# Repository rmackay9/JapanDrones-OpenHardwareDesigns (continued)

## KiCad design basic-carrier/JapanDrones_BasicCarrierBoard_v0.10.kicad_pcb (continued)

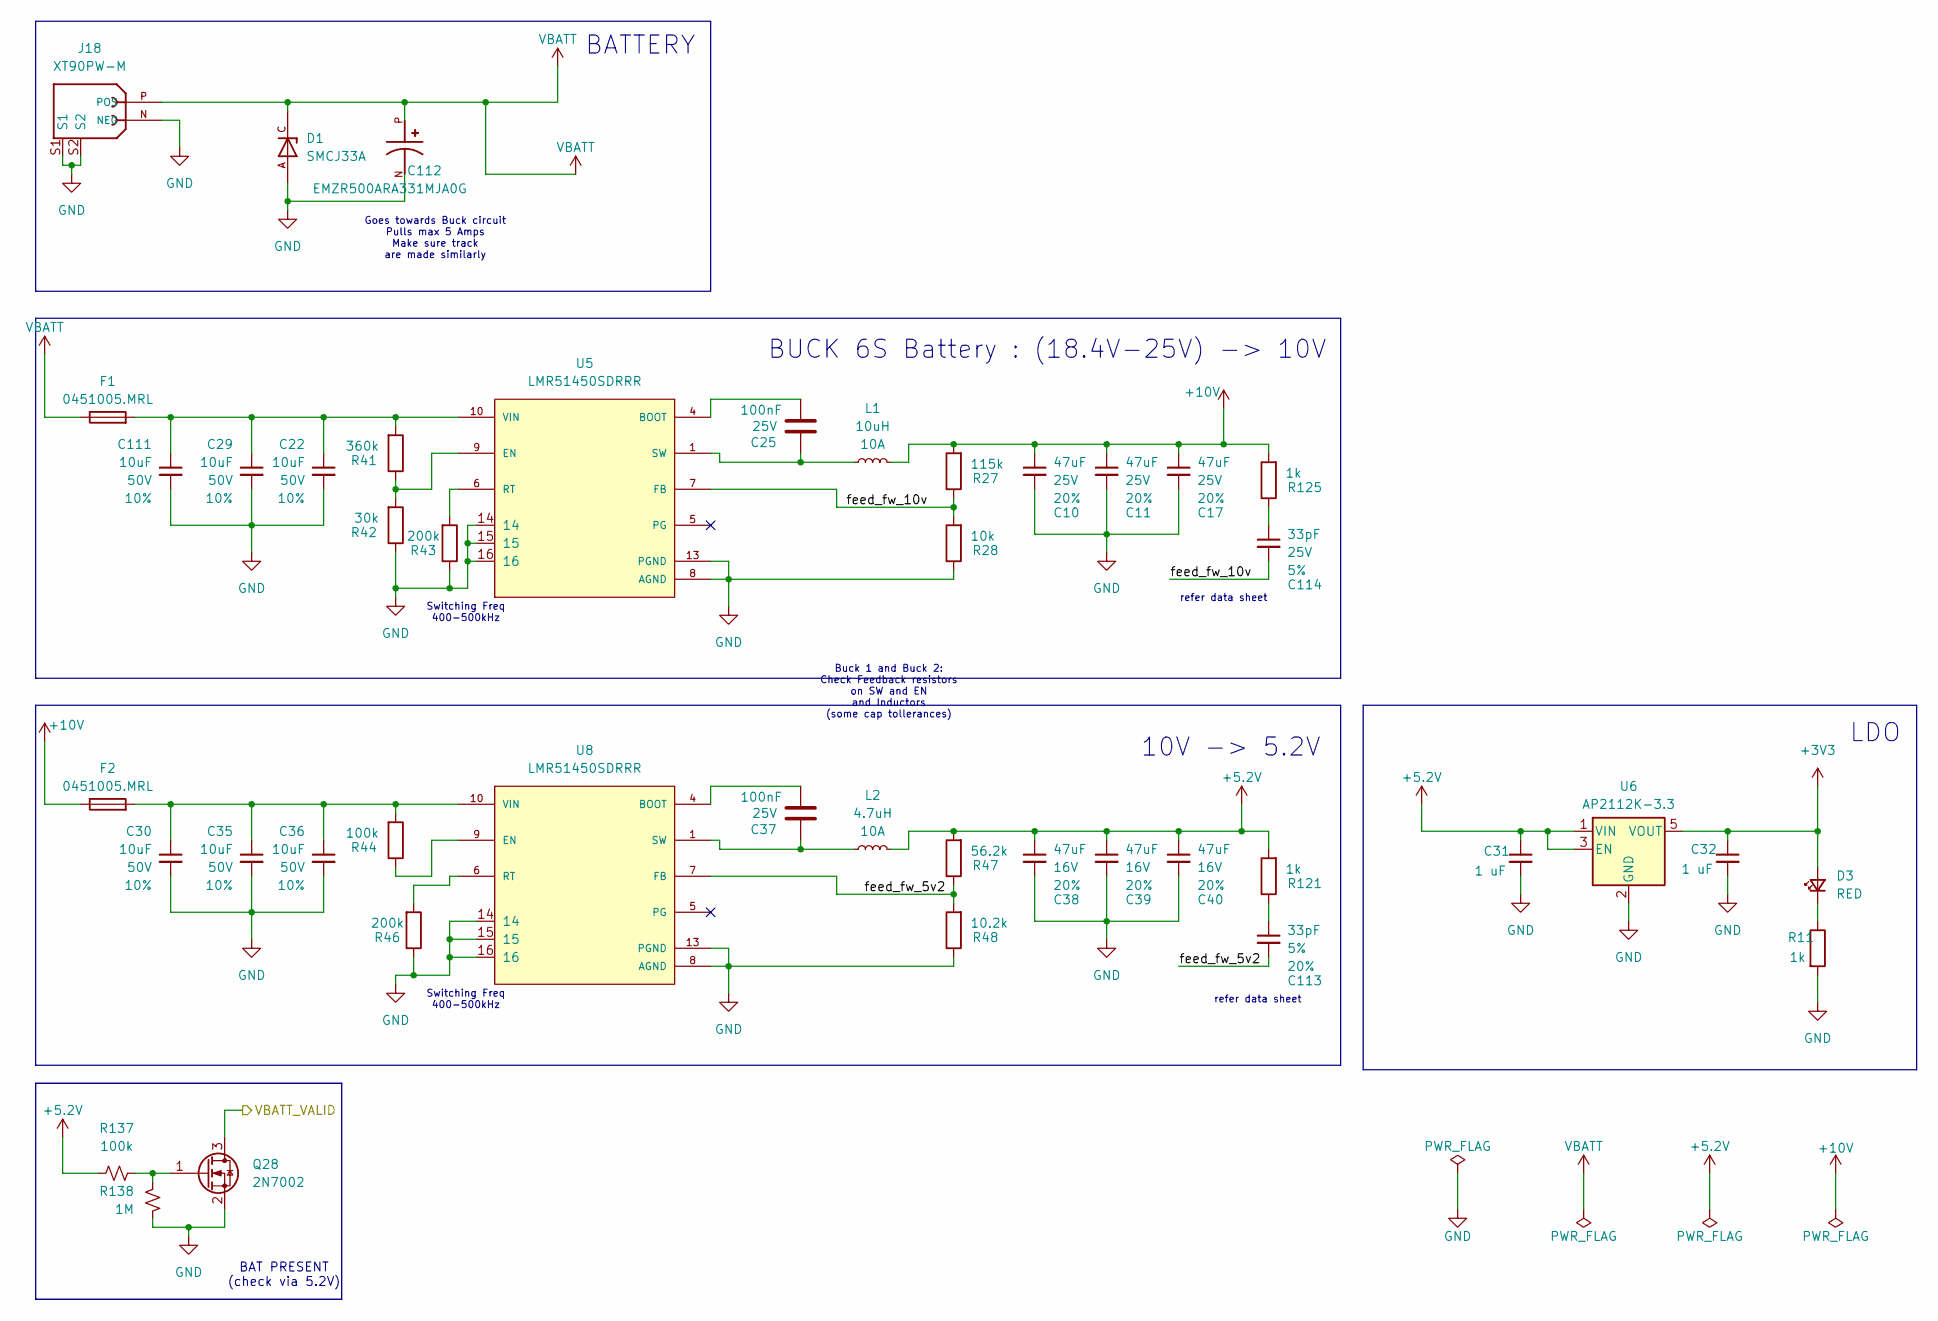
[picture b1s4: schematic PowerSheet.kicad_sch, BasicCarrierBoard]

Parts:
C10, C11, C17: 47uF; C_1206_3216Metric; Voltage 25V; Tolerance 20%; MPN GRM31CR61E476ME44L; LCSC C403725
C22, C29, C30, C35, C36, C111: 10uF; C_1206_3216Metric; Voltage 50V; Tolerance 10%; MPN CL31B106KBHNNNE; LCSC C89632
C25, C37: 100nF; C_0603_1608Metric; Voltage 25V; MPN CL10B104KB8NNNC; LCSC C1591
C31, C32: 1 uF; C_0603_1608Metric; Voltage 1kV; Tolerance 100%; MPN CL10B105KO8NNNC; LCSC Part C5673
C38, C39, C40: 47uF; C_1206_3216Metric; Voltage 16V; Tolerance 20%; MPN GRM31CR61E476ME44L; LCSC C403725
C112: EMZR500ARA331MJA0G; CAPAE1030X1050N; PARTREV N/A; LCSC C1845422
C113: 33pF; C_0603_1608Metric; Voltage 5%; Tolerance 20%; MPN CL10C330JB8NNNC; LCSC C1663
C114: 33pF; C_0603_1608Metric; Voltage 25V; Tolerance 5%; MPN CL10C330JB8NNNC; LCSC C1663
D1: SMCJ33A; DIOM6859X262N; PARTREV R2102; LCSC C42371548
D3: RED; LED_0603_1608Metric; MPN KT-0603R; LCSC Part C2286
F1, F2: 0451005.MRL; FUSC6125X236N; MPN 0451005.MRL; LCSC C48467
J18: XT90PW-M; AMASS_XT90PW-F; PARTREV V00; LCSC C3040689
L1: 10uH; COILMX MSY1040-100M-V; MPN MSY1040-100M-V; LCSC C49328996
L2: 4.7uH; APS1040M4R7H_4.7uh; MPN APS1040M4R7H; LCSC C49073686
Q28: 2N7002; SOT-23; MPN 2N7002; LCSC C8545
R11: 1k; R_0603_1608Metric; MPN 0603WAF1001T5E; LCSC Part C21190
R27: 115k; R_0603_1608Metric; MPN 0603WAF1153T5E; LCSC C22783
R28: 10k; R_0603_1608Metric; MPN 0603WAF1002T5E; LCSC C25804
R41: 360k; R_0603_1608Metric; MPN 0603WAF3603T5E; LCSC C23146
R42: 30k; R_0603_1608Metric; MPN 0603WAF3002T5E; LCSC C22984
R43, R46: 200k; R_0603_1608Metric; MPN 0603WAF2003T5E; LCSC C25811
R44: 100k; R_0603_1608Metric; MPN 0603WAF1003T5E; LCSC C25803
R47: 56.2k; R_0603_1608Metric; MPN 0603WAF5622T5E; LCSC C23080
R48: 10.2k; R_0603_1608Metric; MPN 0603WAF1022T5E; LCSC C22772
R121, R125: 1k; R_0603_1608Metric; MPN 0603WAF1001T5E; LCSC C21190
R137: 100k; R_0402_1005Metric; MPN 0402WGF1003TCE; LCSC C25741
R138: 1M; R_0402_1005Metric; MPN 0402WGF1004TCE; LCSC C26083
U5, U8: LMR51450SDRRR; CONV_LMR51450SDRRR; PARTREV December 2022; LCSC C6890985
U6: AP2112K-3.3; SOT-23-5_HandSoldering; MPN AP2112K-3.3TRG1; LCSC Part C23380830

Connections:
+3V3: C32.1, D3.2 (A), U6.5 (VOUT); also elsewhere on the board
+5.2V: C31.1, C38.1, C39.1, C40.1, L2.2, R47.2, R121.2, R137.1, U6.1 (VIN), U6.3 (EN); also elsewhere on the board
+10V: C10.1, C11.1, C17.1, F2.1, L1.2, R27.2, R125.2; also elsewhere on the board
/Connectors/VBATT_VALID: Q28.3 (D); also elsewhere on the board
/PowerSheet/feed_fw_5v2: C113.2, R47.1, R48.2, U8.7 (FB)
/PowerSheet/feed_fw_10v: C114.2, R27.1, R28.2, U5.7 (FB)
GND: C10.2, C11.2, C17.2, C22.2, C29.2, C30.2, C31.2, C32.2, C35.2, C36.2, C38.2, C39.2, C40.2, C111.2, C112.N, D1.A, J18.N (NEG), J18.S1, J18.S2, Q28.2 (S), R11.2, R28.1, R42.1, R43.1, R46.1, R48.1, R138.1, U5.8 (AGND), U5.13 (PGND), U5.14, U5.15, U5.16, U6.2 (GND), U8.8 (AGND), U8.13 (PGND), U8.14, U8.15, U8.16; also elsewhere on the board
unnamed: C25.2, L1.1, U5.1 (SW), U5.2 (SW), U5.3 (SW)
unnamed: C30.1, C35.1, C36.1, F2.2, R44.2, U8.10 (VIN), U8.11 (VIN), U8.12 (VIN)
unnamed: C37.2, L2.1, U8.1 (SW), U8.2 (SW), U8.3 (SW)
unnamed: C22.1, C29.1, C111.1, F1.2, R41.2, U5.10 (VIN), U5.11 (VIN), U5.12 (VIN)
unnamed: C113.1, R121.1
unnamed: C114.1, R125.1
unnamed: D3.1 (K), R11.1
unnamed: Q28.1 (G), R137.2, R138.2
unnamed: C25.1, U5.4 (BOOT)
unnamed: R41.1, R42.2, U5.9 (EN)
unnamed: R43.2, U5.6 (RT)
unnamed: C37.1, U8.4 (BOOT)
unnamed: R44.1, U8.9 (EN)
unnamed: R46.2, U8.6 (RT)
VBATT: C112.P, D1.C, F1.1, J18.P (POS); also elsewhere on the board

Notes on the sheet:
refer data sheet
Goes towards Buck circuit Pulls max 5 Amps Make sure track are made similarly
BUCK 6S Battery : (18.4V-25V) -> 10V
Switching Freq 400-500kHz
BATTERY
LDO
BAT PRESENT (check via 5.2V)
10V -> 5.2V
Buck 1 and Buck 2: Check Feedback resistors on SW and EN and Inductors (some cap tollerances)

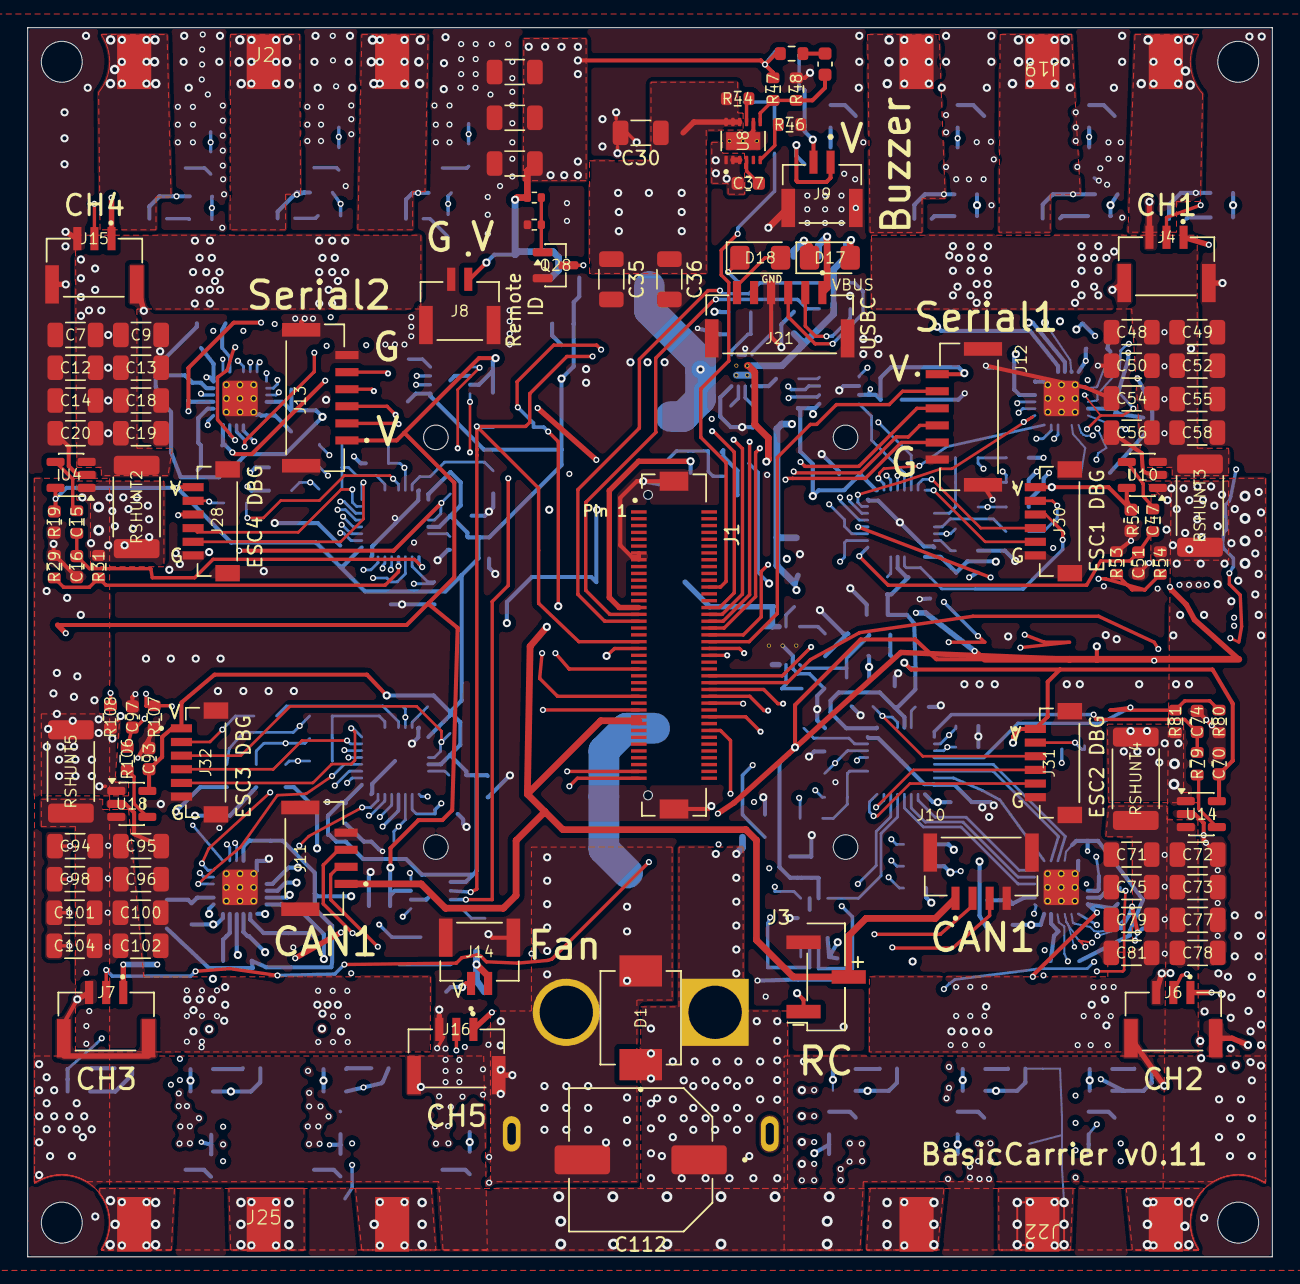
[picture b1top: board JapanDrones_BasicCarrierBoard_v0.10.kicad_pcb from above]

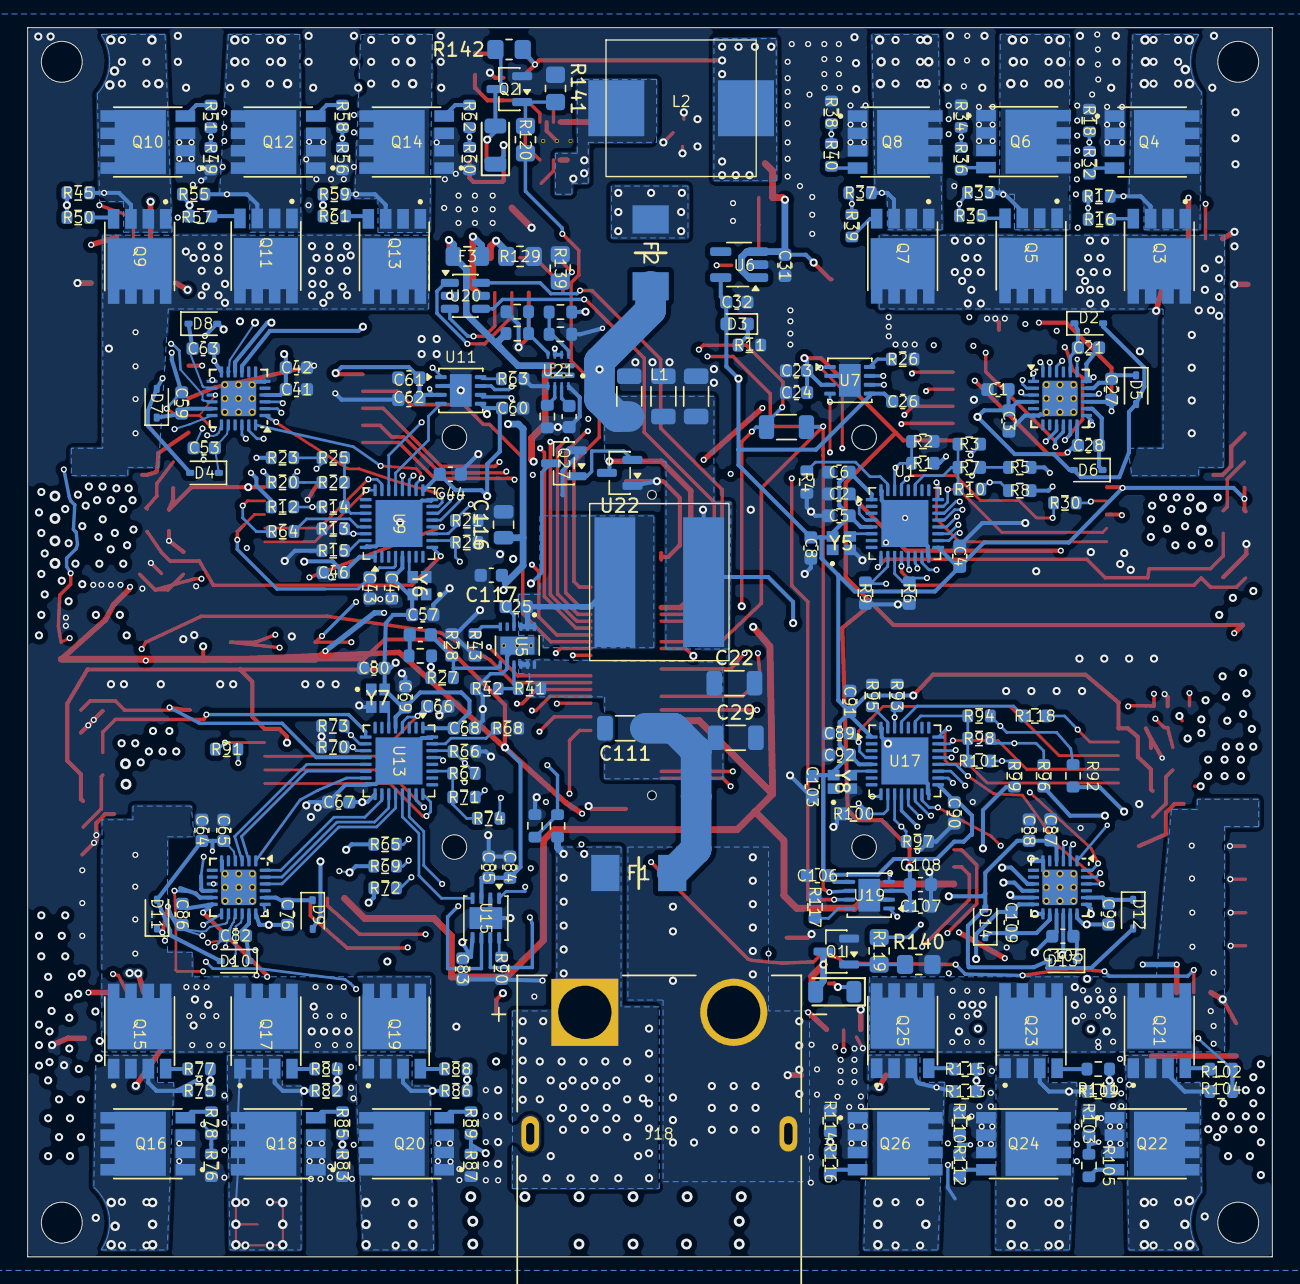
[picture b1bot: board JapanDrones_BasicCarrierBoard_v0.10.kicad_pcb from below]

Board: 6 copper layers, 91.1 x 90.0 mm, 356 parts (252 on the bottom side), 231 nets.

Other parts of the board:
C116: 47uF; C_0805_2012Metric
C117: 100nF; C_0603_1608Metric
U22: TCM809JENB713; SOT-23

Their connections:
/Connectors/POW_SEL: C116.1, C117.1; also elsewhere on the board
/USBSheet/VBUS: U22.3 (VCC); also elsewhere on the board
GND: C116.2, C117.2, U22.1 (GND); also elsewhere on the board
unnamed 208: U22.2 (~RESET); also elsewhere on the board

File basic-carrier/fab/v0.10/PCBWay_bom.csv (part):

Designator,Quantity,Value,Footprint,Package,MPN,DNP,Mount_Type,Description,LCSC,MF,PROD_ID,Voltage,Tolerance,Temperature Coefficient,MAXIMUM_PACKAGE_HEIGHT,Check_prices,STANDARD,PARTREV,SnapEDA_Link,MP,MANUFACTURER,SNAPEDA_PACKAGE_ID,LCSC Part,SNAPEDA_PN,Current,MNP,Power
"C1, C108, C24, C41, C62, C64, C85, C87",8,10uF,C_0603_1608Metric,,CL10A106MA8NRNC,,smt,Unpolarized capacitor,C96446,Samsung Electro-Mechanics,,,,,,,,,,,,,,,,,
"C10, C11, C17, C38, C39, C40",6,47uF,C_1206_3216Metric,,GRM31CR61E476ME44L,,smt,Unpolarized capacitor,C403725,Murata Electronics,CAP-10300,"[C10,C11,C17]25V; [C38,C39,C40]16V",20%,Y5V,,,,,,,,,,,,,
"C100, C101, C102, C104, C12, C13, C14, C18, C19, C20, C48, C49, C50, C52, C54, C55, C56, C58, C7, C71, C72, C73, C75, C77, C78, C79, C81, C9, C94, C95, C96, C98",32,10uF,C_1206_3216Metric,,CL31B106KBHNNNE,,smt,Unpolarized capacitor,C89632,Samsung Electro-Mechanics,,,,,,,,,,,,,,,,,
"C103, C106, C107, C110, C15, C16, C2, C23, C25, C26, C3, C37, C4, C42, C43, C44, C45, C46, C47, C5, C51, C57, C6, C60, C61, C65, C66, C67, C68, C69, C70, C74, C8, C80, C83, C84, C88, C89, C90, C91, C92, C93, C97",43,100nF,C_0603_1608Metric,,CL10B104KB8NNNC,,smt,Unpolarized capacitor,C1591,Samsung Electro-Mechanics,CAP-00000,"[C110]10V; [C25,C37]25V",100%,,,,,,,,,,,,,,
"C105, C109, C21, C27, C28, C53, C59, C63, C76, C82, C86, C99",12,1uF,C_0603_1608Metric,,CL10B105KA8NNNC,,smt,Unpolarized capacitor,C29936,Samsung Electro-Mechanics,,,,,,,,,,,,,,,,,
C111,1,EEEFP1V101AL,CAP_EEEFP1V101AL,,EEE-FP1V101AL,,smt,Cap Aluminum Lytic 100uF 35V 20% (8 X 10.2mm) SMD 0.08 Ohm 850mA 2000h 105°C Automotive T/R,C1881600,PANASONIC,,,,,10.2mm,https://www.snapeda.com/parts/EEEFP1V101AL/Panasonic/view-pa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,Manufacturer Recommendations,10-Oct-19,https://www.snapeda.com/parts/EEEFP1V101AL/Panasonic/view-pa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,EEEFP1V101AL,Panasonic,,,,,,
C112,1,EMZR500ARA331MJA0G,CAPAE1030X1050N,,EMZR500ARA331MJA0G,,smt,"330 µF 50 V Aluminum Electrolytic Capacitors Radial, Can - SMD 120mOhm @ 100kHz 2000 Hrs @ 105°C",C1845422,NCC(Nippon Chemi-Con),,,,,10.5 mm,https://www.snapeda.com/parts/EMZR500ARA331MJA0G/Chemi-Con/v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,IPC 7351B,N/A,https://www.snapeda.com/parts/EMZR500ARA331MJA0G/Chemi-Con/v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,EMZR500ARA331MJA0G,United Chemi-Con,43265,,,,,
"C113, C114",2,33pF,C_0603_1608Metric,,CL10C330JB8NNNC,,smt,Unpolarized capacitor,C1663,Samsung Electro-Mechanics,CAP-10300,[C113]5%; [C114]25V,[C113]20%; [C114]5%,Y5V,,,,,,,,,,,,,
"C22, C29, C35, C36",4,10uF,C_1210_3225Metric,,CC1210X7R50V106KN,,smt,Unpolarized capacitor,C53084452,TORCH,CAP-09824,50V,10%,,,,,,,,,,,,,,
C30,1,EEEFK1C221P,CAP_EEEFK1C221P,,EEEFK1C221P,,smt,"220µF 16V Aluminum Electrolytic Capacitors Radial, Can - SMD 2000 Hrs @ 105°C",C178534,PANASONIC,,,,,6.2mm,https://www.snapeda.com/parts/EEE-FK1C221P/Panasonic/view-pa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,Manufacturer Recommendations,10-Oct-19,https://www.snapeda.com/parts/EEE-FK1C221P/Panasonic/view-pa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,EEE-FK1C221P,Panasonic,,,,,,
"C31, C32",2,1 uF,C_0603_1608Metric,,CL10B105KO8NNNC,,smt,https://robu.in/product/1206b105k500nt-fh-50v-1uf-x7r%c2%b11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,C59782,Samsung Electro-Mechanics,CAP-00000,1kV,100%,,,,,,,,,,C5673,,,,
D1,1,SMCJ33A,DIOM6859X262N,,SMCJ33A,,smt,"1500W, 33V, Unidirectional, TVS",C42371548,hongjiacheng,,,,,2.62 mm,https://www.snapeda.com/parts/SMCJ33A/taiwan/view-part/?ref=eda,IPC-7351B,R2102,https://www.snapeda.com/parts/SMCJ33A/taiwan/view-part/?ref=snap,SMCJ33A,Taiwan Semiconductor,,,,,,
"D10, D11, D12, D13, D14, D2, D4, D5, D6, D7, D8, D9",12,1N5819WS,D_SOD-323,,1N5819WS,,smt,Zener diode,C191023,Guangdong Hottech,,,,,,,,,,,,,,,,,
"D15, D16",2,SS14,D_SOD-123FL,,SS14L,,smt,https://www.ktron.in/product/ss14-diode-sod-123/,C190475,Guangdong Hottech,,,,,,,,,,,,,,,,,
"D17, D18",2,LED,LED_1206_3216Metric_Pad1.42x1.75mm_HandSolder,,KT-1206R,,smt,https://www.ktron.in/product/smd-yellow-led-1206/,C49018,Hubei KENTO Elec,LED-,,,,,,,,,,,,,,,,
D3,1,RED,LED_0603_1608Metric,,KT-0603R,,smt,Light emitting diode,C2286,Hubei KENTO Elec,LED-,,,,,,,,,,,,C2286,,,,
"F1, F2",2,0451005.MRL,FUSC6125X236N,,0451005.MRL,,smt,Fuse,C48467,Littelfuse,,,,,,,,,,,,,,,,,
F3,1,500mA,Fuse_0805_2012Metric_Pad1.15x1.40mm_HandSolder,,ASMD0805-050,,smt,https://www.ktron.in/product/asmd0805-050-shenzhen-jdt-fuse/,C135329,Shenzhen JDT Fuse,,,,,,,,,,,,,,,,,
J1,1,DF17_2.0_-80DP-0.5V_57_,HRS_DF17_2.0_-80DP-0.5V_57_,,DF17(2.0)-80DP-0.5V(57),,smt,"80 Position Connector Header, Outer Shroud Contacts Surface Mount Gold",C3642153,Hirose Electric,,,,,,https://www.snapeda.com/parts/DF17(2.0)-80DP-0.5V(57)/Hirose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,,,https://www.snapeda.com/parts/DF17(2.0)-80DP-0.5V(57)/Hirose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,DF17(2.0)-80DP-0.5V(57),HRS(Hirose),,,,,,
"J10, J11",2,BM04B-GHS-TBT_LF__SN__N_,JST_BM04B-GHS-TBT_LF__SN__N_,,BM04B-GHS-TBT(LF)(SN),,smt,Connector Header Surface Mount 4 position 0.049 (1.25mm),C161692,JST Sales,,,,,4.05mm,https://www.snapeda.com/parts/BM04B-GHS-TBT(LF)(SN)(N)/JST/v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,Manufacturer Recommendations,N/A,https://www.snapeda.com/parts/BM04B-GHS-TBT(LF)(SN)(N)/JST/v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,BM04B-GHS-TBT(LF)(SN)(N),JST,,,,,,
"J12, J13, J21",3,BM06B-GHS-TBT_LF__SN__N_,JST_BM06B-GHS-TBT_LF__SN__N_,,BM06B-GHS-TBT(LF)(SN),,smt,Connector Header Surface Mount 6 position 0.049 (1.25mm),C189892,JST Sales,,,,,4.05mm,https://www.snapeda.com/parts/BM06B-GHS-TBT(LF)(SN)(N)/JST/v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,Manufacturer Recommendations,N/A,https://www.snapeda.com/parts/BM06B-GHS-TBT(LF)(SN)(N)/JST/v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,BM06B-GHS-TBT(LF)(SN)(N),JST,,,,,,
"J14, J8, J9",3,BM02B-GHS-TBT_LF__SN__N_,JST_BM02B-GHS-TBT_LF__SN__N_,,BM02B-GHS-TBT(LF)(SN),,smt,Connector Header Surface Mount 2 position 0.049 (1.25mm),C161690,JST Sales,,,,,4.05 mm,https://www.snapeda.com/parts/BM02B-GHS-TBT%20(LF)(SN)(N)/JS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,Manufacturer Recommendations,,https://www.snapeda.com/parts/BM02B-GHS-TBT%20(LF)(SN)(N)/JS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,BM02B-GHS-TBT (LF)(SN)(N),JST,,,,,,
"J15, J16, J4, J6, J7",5,BM03B-GHS-TBT_LF__SN__N_,CONN_BM03B-GHS-TBT_LF__SN__N_,,BM03B-GHS-TBT(LF)(SN),,smt,Connector Header Surface Mount 3 position 0.049 (1.25mm),C161691,JST Sales,,,,,,https://www.snapeda.com/parts/BM03B-GHS-TBT(LF)(SN)(N)/JST/v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,,,https://www.snapeda.com/parts/BM03B-GHS-TBT(LF)(SN)(N)/JST/v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,BM03B-GHS-TBT(LF)(SN)(N),JST Sales America Inc.,,,,,,
J18,1,XT90PW-F,AMASS_XT90PW-F,,XT90PW-F30.G.Y,,tht,"Socket, DC supply, XT90, female, PIN:2, on PCBs, THT",C3040690,Changzhou Amass Elec,,,,,10.3 mm,https://www.snapeda.com/parts/XT90PW-F/AMASS/view-part/?ref=eda,Manufacturer Recommendations,V00,https://www.snapeda.com/parts/XT90PW-F/AMASS/view-part/?ref=snap,XT90PW-F,AMASS,,,,,,
"J28, J30, J31, J32",4,BM06B-SRSS-TB_LF__SN_,JST_BM06B-SRSS-TB_LF__SN_,,BM06B-SRSS-TB(LF)(SN),,smt,Connector Header Surface Mount 6 position 0.039 (1.00mm),C160392,JST Sales,,,,,6.3 mm,https://www.snapeda.com/parts/BM06B-SRSS-TB%20(LF)(SN)/JST/v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,Manufacturer Recommendations,N/A,https://www.snapeda.com/parts/BM06B-SRSS-TB%20(LF)(SN)/JST/v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,BM06B-SRSS-TB (LF)(SN),JST Sales America Inc.,,,BM06B-SRSS-TB(LF)(SN),,,
J3,1,RC,PinHeader_1x03_P2.54mm_Vertical_SMD_Pin1Right,,2.54-1*3PPin,,smt,"Generic connector, single row, 01x03, script generated",C49257,BOOMELE(Boom Precision Elec),,,,,,,,,,,,,,,,,
L1,1,10uH,COILMX MSY1040-100M-V,,MSY1040-100M-V,,smt,Inductor,C49328996,COILMX,NDUC-17223,,,,,,,,,,,,,,10A,C49328996,
L2,1,4.7uH,APS1040M4R7H_4.7uh,,APS1040M4R7H,,smt,Inductor,C49073686,COILANK INTERNATIONAL,NDUC-17223,,,,,,,,,,,,,,10A,C49328996,
"Q1, Q2",2,AO3400A,SOT-23,,AO3400A,,smt,"30V Vds, 5.7A Id, N-Channel MOSFET, SOT-23",C20917,Alpha & Omega Semicon,,,,,,,,,,,,,,,,,
"Q10, Q11, Q12, Q13, Q14, Q15, Q16, Q17, Q18, Q19, Q20, Q21, Q22, Q23, Q24, Q25, Q26, Q3, Q4, Q5, Q6, Q7, Q8, Q9",24,TPHR8504PL_L1Q,TRANS_TPHR8504PL_L1Q,,"TPHR8504PL,L1Q(M",,smt,"N-Channel 40 V 150A (Tc) 1W (Ta), 170W (Tc) Surface Mount 8-SOP Advance (5x5)",C5331611,TOSHIBA,,,,,,"https://www.snapeda.com/parts/TPHR8504PL,L1Q/Toshiba/view-part/?ref=eda",Manufacturer Recommendations,3,"https://www.snapeda.com/parts/TPHR8504PL,L1Q/Toshiba/view-part/?ref=snap","TPHR8504PL,L1Q",TOSHIBA,,,,,,
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
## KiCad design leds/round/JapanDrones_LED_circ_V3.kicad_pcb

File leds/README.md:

# JapanDrones LEDs

Two small RGB LED boards used on the JapanDrones aerial photography copter.

| Round, top | Round, bottom | Rectangular, top | Rectangular, bottom |
|---|---|---|---|
|  |  |  |  |

| Board | Folder | Size | Use |
|---|---|---|---|
| Round (V3) | [round/](round/) | 25 mm diameter | Mounted under each motor at the end of the arms |
| Rectangular (V4) | [rect/](rect/) | 29 x 6.6 mm | Mounted at the back of the vehicle so the pilot can easily see the vehicle's status |

Both boards share the same circuit:

- 2x SK6812 addressable RGB LEDs (NeoPixel compatible)
- JST-GH 3 pin connector (SM03B-GHS-TB): VCC (5V), GND, data
- 330R series resistor and TVS diode protecting the data input, plus decoupling capacitors

They work with ArduPilot's NeoPixel / SK6812 LED support (e.g. `SERVOx_FUNCTION` = NeoPixel and `NTF_LED_TYPES`).

## Files in each board folder

| File | What it is |
|---|---|
| `*.kicad_pro`, `*.kicad_sch`, `*.kicad_pcb` | KiCad 9 project, schematic and PCB. All symbols and footprints are embedded so no extra libraries are needed |
| `fab/*-fab.zip` | Gerber and drill files (plus the original PCBWay BOM, positions and netlist). This is the exact zip PCBWay built from |
| `fab/bom.csv` | Bill of materials (parts list) with manufacturer part numbers (the parts PCBWay actually fitted), alternates and LCSC numbers |
| `fab/positions.csv` | Pick and place (a.k.a. centroid or CPL) file: the X/Y position, rotation and side of each part, used by the assembly machine |
| `3d/*.step` | 3D model of the assembled board for mechanical CAD (Fusion 360, FreeCAD, SolidWorks, ...) |
| `3d/*.stl` | Mesh of the assembled board. Click it on GitHub to view it in 3D |
| `docs/*.png` | KiCad renders of the top and bottom of the board |

## Ordering

### PCBWay (PCB + assembly)

1. Go to PCBWay's PCB instant quote and upload `fab/<board>-fab.zip`
2. Board options: 2 layers, 1.6 mm thickness (other options as you prefer)
3. Select "Assembly service". The round board has parts on the top side only, the rectangular board has parts on both sides
4. Upload `fab/bom.csv` and `fab/positions.csv` when asked for the BOM and centroid files

Note: the SK6812 LEDs are moisture sensitive and should be baked before reflow (PCBWay does this automatically).

### Other manufacturers

The zip contains standard Gerber (RS-274X) and Excellon drill files, which any PCB manufacturer accepts.
For assembly, most services (JLCPCB, Seeed, Elecrow, ...) accept a BOM and pick and place CSV, though column names may need to be adjusted to match their template.
You can also re-generate the files in your manufacturer's preferred format by opening the `.kicad_pcb` in KiCad 9.

## Licence

[CERN-OHL-S-2.0](../LICENSE.txt)

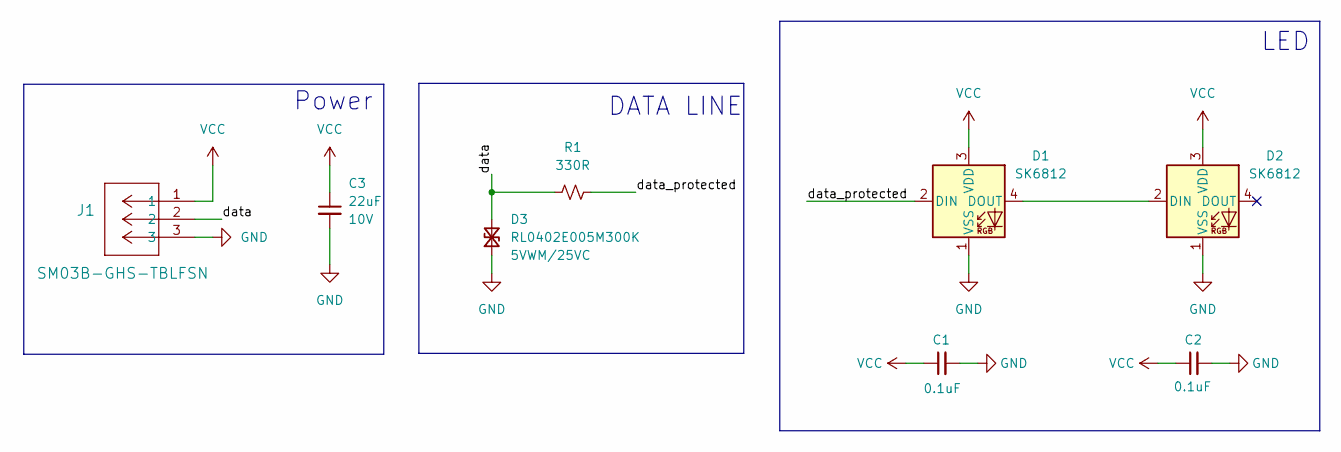
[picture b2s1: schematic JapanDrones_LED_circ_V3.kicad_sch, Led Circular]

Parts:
C1, C2: 0.1uF; C_0603_1608Metric; Voltage 50V; Tolerance 10%; MPN CC0603KRX7R9BB104; LCSC C14663
C3: 22uF; C_1206_3216Metric_Pad1.33x1.80mm_HandSolder; Voltage 10V; Tolerance 10%; MPN 1206X226K100NT; LCSC C1859
D1, D2: SK6812; LED_SK6812_PLCC4_5.0x5.0mm_P3.2mm; MPN SK6812; LCSC C5378720
D3: RL0402E005M300K; C_0402_1005Metric; Rating 5VWM/25VC; MPN RL0402E005M300K; LCSC C20950
J1: SM03B-GHS-TBLFSN; CONN_SM03B-GHS-TBLFSN_JST; MPN SM03B-GHS-TB(LF)(SN); LCSC C225126
R1: 330R; R_0603_1608Metric; Tolerance 1%; MPN 0603WAF3300T5E; LCSC C23138

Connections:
/data: D3.2 (A2), J1.2, R1.1
/data_protected: D1.2 (DIN), R1.2
GND: C1.2, C2.2, C3.2, D1.1 (VSS), D2.1 (VSS), D3.1 (A1), J1.3
unnamed: D1.4 (DOUT), D2.2 (DIN)
VCC: C1.1, C2.1, C3.1, D1.3 (VDD), D2.3 (VDD), J1.1

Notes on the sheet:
Power
DATA LINE
LED

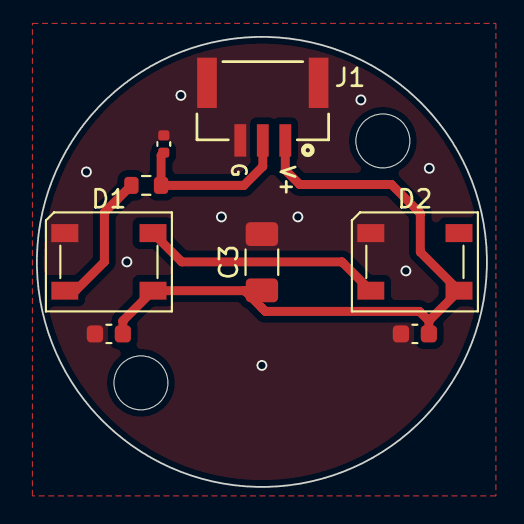
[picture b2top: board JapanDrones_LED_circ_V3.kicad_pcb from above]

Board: 2 copper layers, 25.0 x 25.0 mm, 8 parts (0 on the bottom side), 5 nets.

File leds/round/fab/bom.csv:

Designator,Qty,Value,Description,Package,Manufacturer,MPN,Alternate (Manufacturer MPN),LCSC,Notes
"C1,C2",2,100nF,"Ceramic capacitor, 50V, X7R, 10%",0603,YAGEO,CC0603KRX7R9BB104,,C14663,Any 100nF 0603 X7R rated 16V or higher
C3,1,22uF,"Ceramic capacitor, 10V, 10%",1206,Fenghua (FH),1206X226K100NT,,C1859,Any 22uF 1206 X5R/X7R rated 10V or higher
"D1,D2",2,SK6812,"Addressable RGB LED with integrated controller, 5050",PLCC-4 5.0x5.0mm,OPSCO,SK6812,,C5378720,"Moisture sensitive: bake before reflow"
D3,1,RL0402E005M300K,"Bidirectional TVS diode, 5V working, 25V clamp (data line protection)",0402,Ruilon,RL0402E005M300K,,C20950,
J1,1,SM03B-GHS-TB(LF)(SN),"JST-GH 3 pin 1.25mm pitch right angle SMD header",JST GH SMD 3P,JST,SM03B-GHS-TB(LF)(SN),CJT A1257WR-S-3P,C225126,PCBWay fitted the CJT equivalent
R1,1,330R,"Resistor, 1%, 1/10W",0603,UNI-ROYAL,0603WAF3300T5E,,C23138,Any 330R 0603

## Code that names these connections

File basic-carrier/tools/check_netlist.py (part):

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CUBE_REF = "J1"

# Alternate functions of MCU pins used on this board (the symbols only carry
# the GPIO name). STM32L431KC: PA11=CAN1_RX, PA12=CAN1_TX (AF9), PB6=USART1_TX,
# PB7=USART1_RX, PA9=USART1_TX, PA10=USART1_RX, PA2=USART2_TX, PA3=USART2_RX.
PIN_HINTS = {
    "STM32L431": {"PA11": "CAN_RX", "PA12": "CAN_TX", "PB6": "USART1_TX",
                  "PB7": "USART1_RX", "PA9": "USART1_TX", "PA10": "USART1_RX",
                  "PA2": "USART2_TX", "PA3": "USART2_RX"},
}

DRIVER_TYPES = {"output", "tri_state", "power_out"}
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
